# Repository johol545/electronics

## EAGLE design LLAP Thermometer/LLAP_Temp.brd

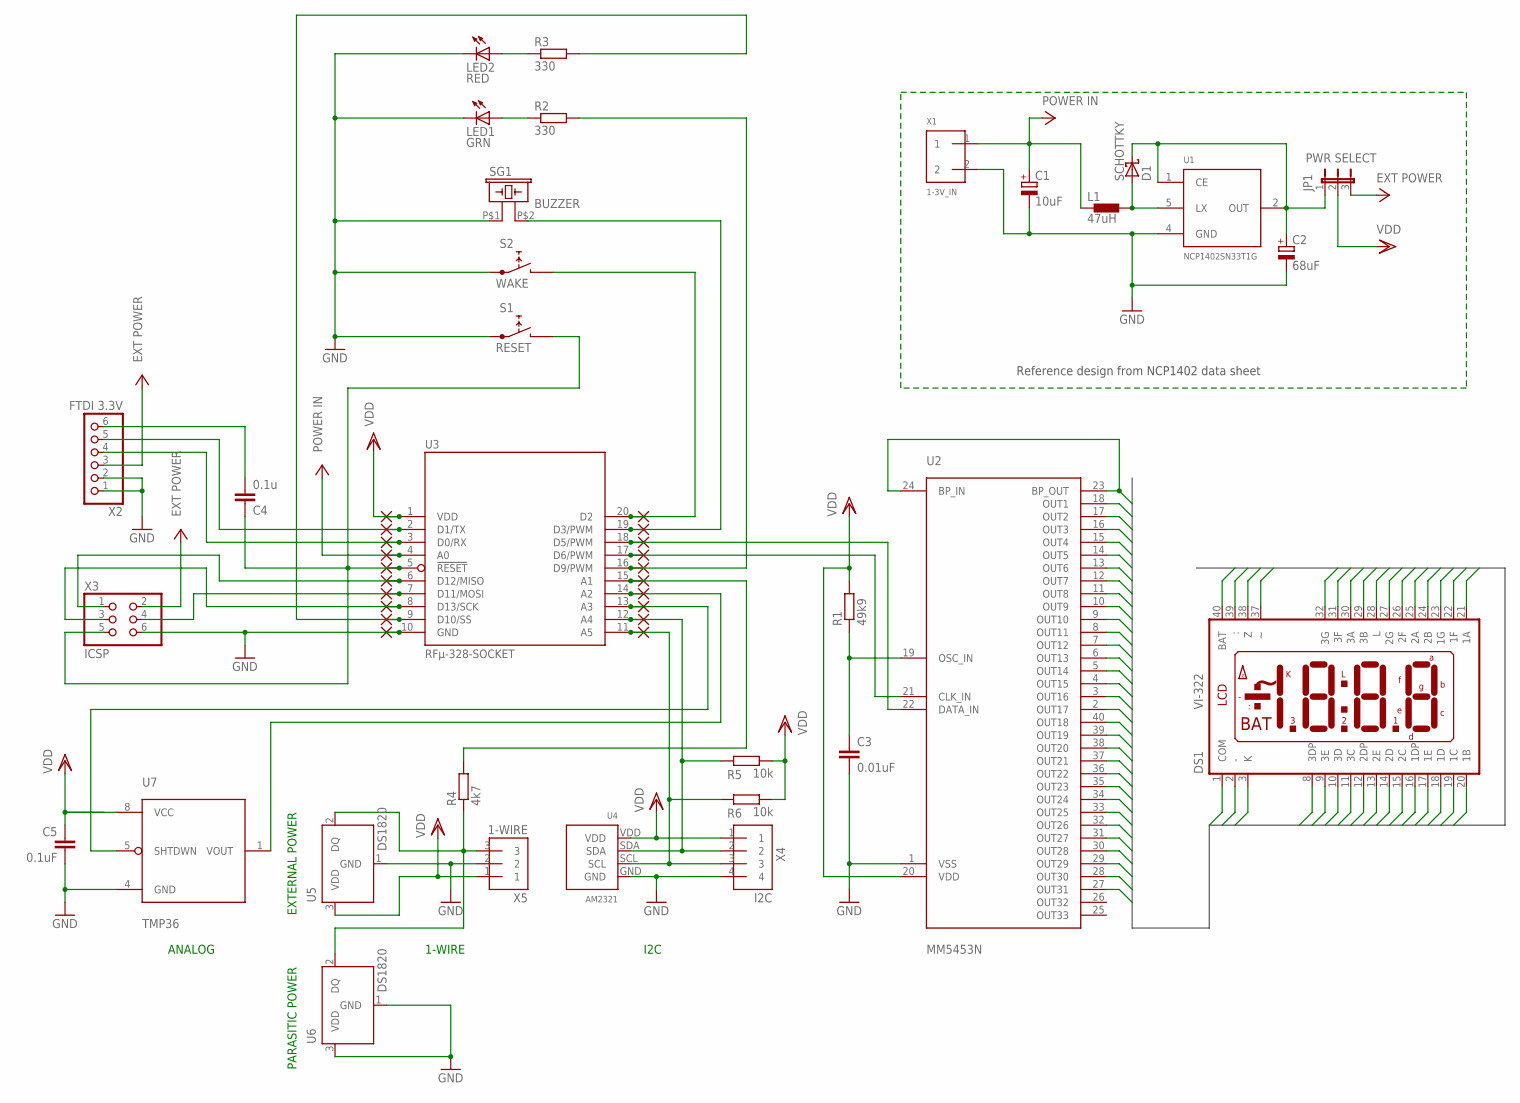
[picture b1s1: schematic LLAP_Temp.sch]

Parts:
C1: 10uF; EIA6032–25
C2: 68uF; EIA7343-31
C3: 0.01uF; C0805
C4: 0.1u; C0805
C5: 0.1uF; C0805
D1: SCHOTTKY; SOT-123_DIODE
DS1: VI-322; LCD-VARITRONIX-VI-322
JP1: PWR SELECT; JP2
L1: 47uH; SRN5040
LED1: GRN; LED3MM
LED2: RED; LED3MM
PAD1: VDD; PAD_1,6/0,9
PAD2: TX; PAD_1,6/0,9
PAD3: RX; PAD_1,6/0,9
PAD4: BATT V.; PAD_1,6/0,9
PAD5: RST; PAD_1,6/0,9
PAD6: MISO; PAD_1,6/0,9
PAD7: MOSI; PAD_1,6/0,9
PAD8: SCK; PAD_1,6/0,9
PAD9: LED2; PAD_1,6/0,9
PAD10: GND; PAD_1,6/0,9
PAD11: SCL; PAD_1,6/0,9
PAD12: SDA; PAD_1,6/0,9
PAD13: TMP SHTDWN; PAD_1,6/0,9
PAD14: TMP MEAS.; PAD_1,6/0,9
PAD15: 1-WIRE; PAD_1,6/0,9
PAD16: LED1; PAD_1,6/0,9
PAD17: LCD CLK; PAD_1,6/0,9
PAD18: LCD DATA; PAD_1,6/0,9
PAD19: BUZZER; PAD_1,6/0,9
PAD20: WAKE BTN; PAD_1,6/0,9
R1: 49k9; R0805
R2, R3: 330; R0805
R4: 4k7; R0805
R5, R6: 10k; R0805
S1: RESET; SWITCH-MJTP12XX
S2: WAKE; SWITCH-MJTP12XX
SG1: BUZZER; BUZZER-PUI_AUDIO-AT-1340-TT-R
U1: NCP1402SN33T1G; SOT23-5L
U2: MM5453N; DIL40
U3: RFµ-328-SOCKET
U4: AM2321
U5, U6: DS1820; TO-92
U7: TMP36; SOIC8
X1: 1-3V_IN; CON-AMP-440055-2
X2: FTDI 3.3V; 1X06
X3: ICSP; 2X03
X4: I2C; CON-AMP-440055-4
X5: 1-WIRE; CON-AMP-440055-3

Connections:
3.3V: C2.P$2 (+), D1.C, JP1.1, U1.1 (CE), U1.2 (OUT)
BP: DS1.1 (COM), U2.23 (BP_OUT), U2.24 (BP_IN)
EXT_PWR: JP1.3, X2.3, X3.2
GND: C1.P$1 (-), C2.P$1 (-), C3.2, C5.2, LED1.K (C), LED2.K (C), PAD10.1, S1.P$1 (1), S2.P$1 (1), SG1.P$1 (1), U1.4 (GND), U2.1 (VSS), U3.10 (GND), U4.GND, U5.1 (GND), U6.1 (GND), U6.3 (VDD), U7.4 (GND), X1.2, X2.1, X2.2, X3.6, X4.4, X5.2
LCD1: DS1.21 (1A), U2.18 (OUT1)
LCD2: DS1.20 (1B), U2.17 (OUT2)
LCD3: DS1.19 (1C), U2.16 (OUT3)
LCD4: DS1.18 (1D), U2.15 (OUT4)
LCD5: DS1.17 (1E), U2.14 (OUT5)
LCD6: DS1.22 (1F), U2.13 (OUT6)
LCD7: DS1.23 (1G), U2.12 (OUT7)
LCD8: DS1.16 (1DP), U2.11 (OUT8)
LCD9: DS1.25 (2A), U2.10 (OUT9)
LCD10: DS1.24 (2B), U2.9 (OUT10)
LCD11: DS1.15 (2C), U2.8 (OUT11)
LCD12: DS1.14 (2D), U2.7 (OUT12)
LCD13: DS1.13 (2E), U2.6 (OUT13)
LCD14: DS1.26 (2F), U2.5 (OUT14)
LCD15: DS1.27 (2G), U2.4 (OUT15)
LCD16: DS1.12 (2DP), U2.3 (OUT16)
LCD17: DS1.28 (L), U2.2 (OUT17)
LCD18: DS1.30 (3A), U2.40 (OUT18)
LCD19: DS1.29 (3B), U2.39 (OUT19)
LCD20: DS1.11 (3C), U2.38 (OUT20)
LCD21: DS1.10 (3D), U2.37 (OUT21)
LCD22: DS1.9 (3E), U2.36 (OUT22)
LCD23: DS1.31 (3F), U2.35 (OUT23)
LCD24: DS1.32 (3G), U2.34 (OUT24)
LCD25: DS1.8 (3DP), U2.33 (OUT25)
LCD26: DS1.3 (K), U2.32 (OUT26)
LCD27: DS1.2 (-), U2.31 (OUT27)
LCD28: DS1.39 (:), U2.30 (OUT28)
LCD29: DS1.40 (BAT), U2.29 (OUT29)
LCD30: DS1.38 (Z), U2.28 (OUT30)
LCD31: DS1.37, U2.27 (OUT31)
unnamed: C4.1, PAD5.1, S1.P$2 (2), U3.5 (!RESET), X3.5
unnamed: PAD15.1, R4.2, U3.15 (A1)
unnamed: PAD6.1, U3.6 (D12/MISO), X3.1
unnamed: R4.1, U5.2 (DQ), U6.2 (DQ), X5.3
unnamed: PAD13.1, U3.13 (A3), U7.5 (SHTDWN)
unnamed: LED2.A, R3.1
unnamed: PAD14.1, U3.14 (A2), U7.1 (VOUT)
unnamed: PAD2.1, U3.2 (D1/TX), X2.5
unnamed: PAD3.1, U3.3 (D0/RX), X2.4
unnamed: PAD18.1, U2.22 (DATA_IN), U3.18 (D5/PWM)
unnamed: PAD17.1, U2.21 (CLK_IN), U3.17 (D6/PWM)
unnamed: D1.A, L1.2, U1.5 (LX)
unnamed: C3.1, R1.1, U2.19 (OSC_IN)
unnamed: LED1.A, R2.1
unnamed: PAD16.1, R2.2, U3.16 (D9/PWM)
unnamed: C4.2, X2.6
unnamed: PAD8.1, U3.8 (D13/SCK), X3.3
unnamed: PAD7.1, U3.7 (D11/MOSI), X3.4
unnamed: PAD9.1, R3.2, U3.9 (D10/SS)
unnamed: PAD20.1, S2.P$2 (2), U3.20 (D2)
unnamed: PAD11.1, R6.1, U3.11 (A5), U4.SCL, X4.3
unnamed: PAD12.1, R5.1, U3.12 (A4), U4.SDA, X4.2
unnamed: PAD19.1, SG1.P$2 (2), U3.19 (D3/PWM)
POWER_IN: C1.P$2 (+), L1.1, PAD4.1, U3.4 (A0), X1.1
VDD: C5.1, JP1.2, PAD1.1, R1.2, R5.2, R6.2, U2.20 (VDD), U3.1 (VDD), U4.VDD, U5.3 (VDD), U7.8 (VCC), X4.1, X5.1

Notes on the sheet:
Reference design from NCP1402 data sheet
I2C
1-WIRE
ANALOG
EXTERNAL POWER
PARASITIC POWER

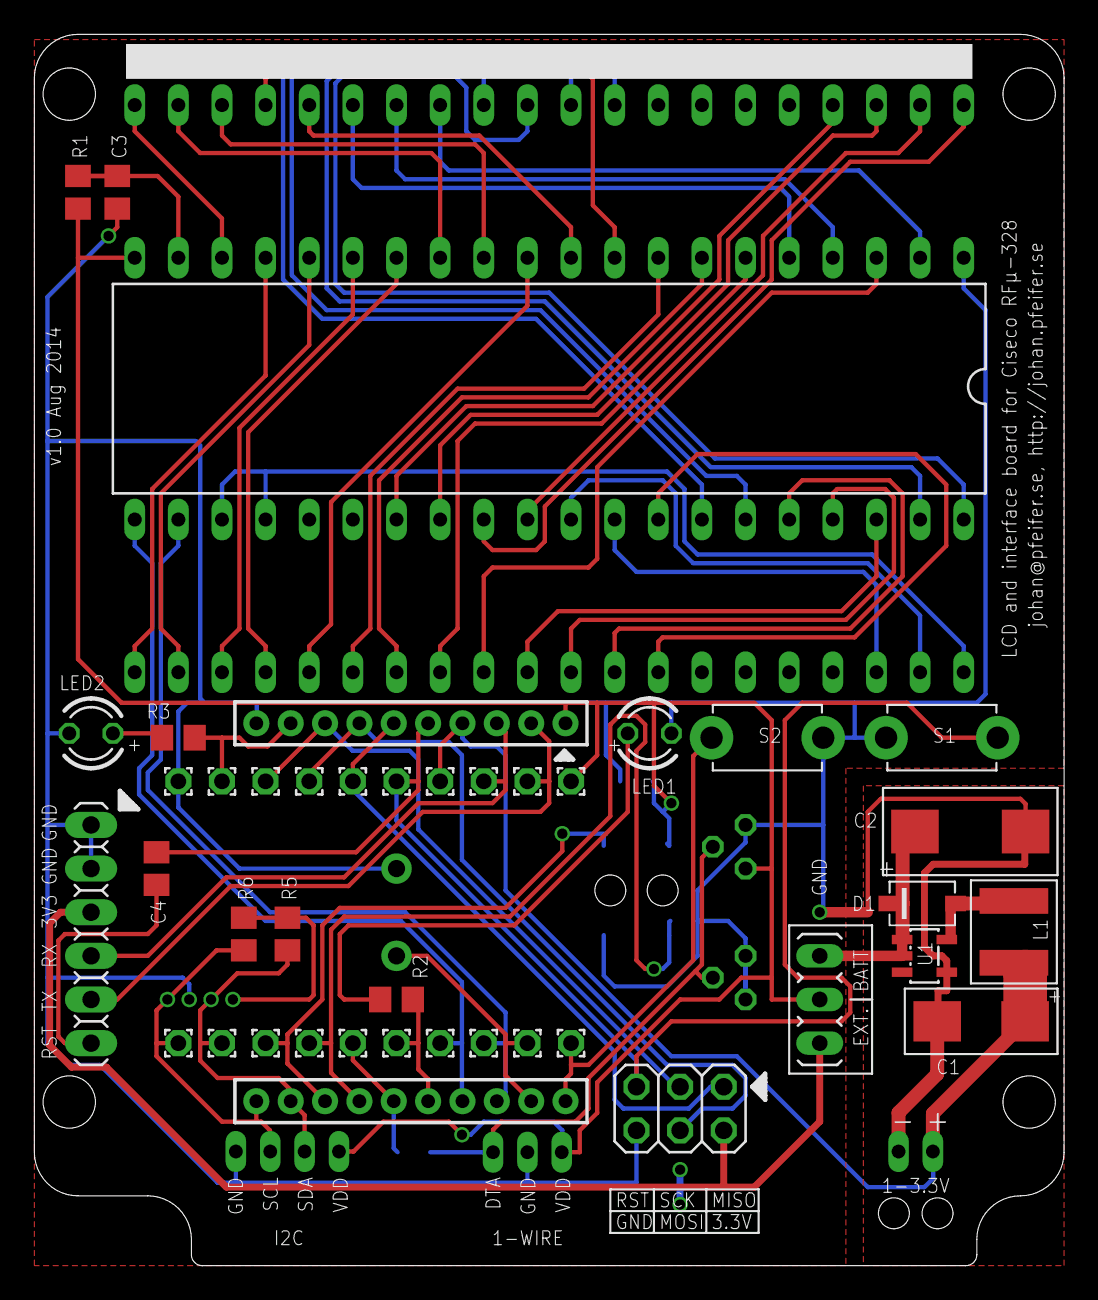
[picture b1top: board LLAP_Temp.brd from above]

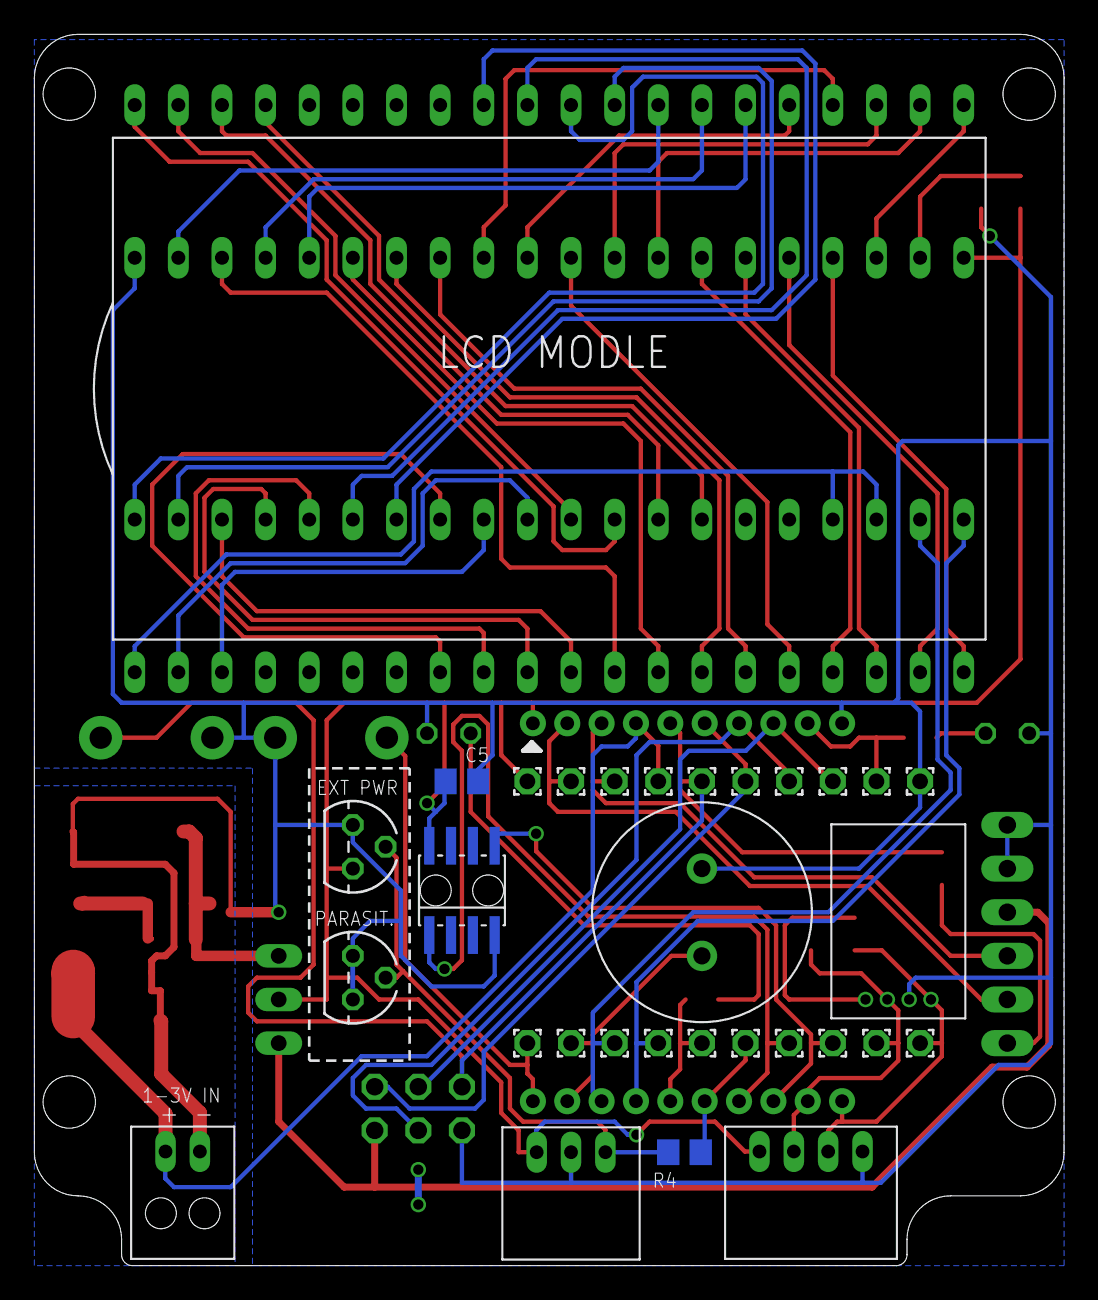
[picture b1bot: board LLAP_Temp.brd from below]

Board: 2 copper layers, 59.9 x 71.7 mm, 52 parts (11 on the bottom side), 60 nets.

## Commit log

2014-08-26 Initial checkin
